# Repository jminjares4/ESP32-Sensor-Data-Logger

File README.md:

# ESP32-Sensor-Data-Logger

<div align='center'>

</div>

## **Hardware**

## **Mechanical**

* The housing was developed by [Rogelio Marco](https://github.com/RogelioMarco) :gear:.

## **Development**
|Microcontroller|Software|Enviroment|Operating System|
| :---| :---| :---| :---|
|  | |  | |

## **Author**
* [**Jesus Minjares** :zap:](https://github.com/jminjares4)<br>
  * Master of Science in Computer Engineering<br>

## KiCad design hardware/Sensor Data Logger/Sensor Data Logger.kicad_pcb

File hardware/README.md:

# Hardware

The hardware was developed through [KiCad](https://www.kicad.org) 6.0. 

## **Development**

## **Features**
- [x] USB-C Battery Charger
  - [x] 1.72 A max current charge
  - [x] Load protection
  - [x] Reverse current protection
- [x] Battery voltage reading 
- [x] MicroSD Card
  - [x] ESD Protection
- [x] Real-Time Clock 
  - [x] External power supply (CR2032)
- [x] External UART to flash ESP32 
- [x] I2C and Analog pins
- [x] Onboard status LEDs 
- [x] Testpoint
  - [x] 3.3V
  - [x] Vbat
  - [x] Ground

## **Schematic**

## **Printed Circuit Board**
### Front View

### Back View

## **Author**
* [**Jesus Minjares** :zap:](https://github.com/jminjares4)<br>
  * Master of Science in Computer Engineering<br>

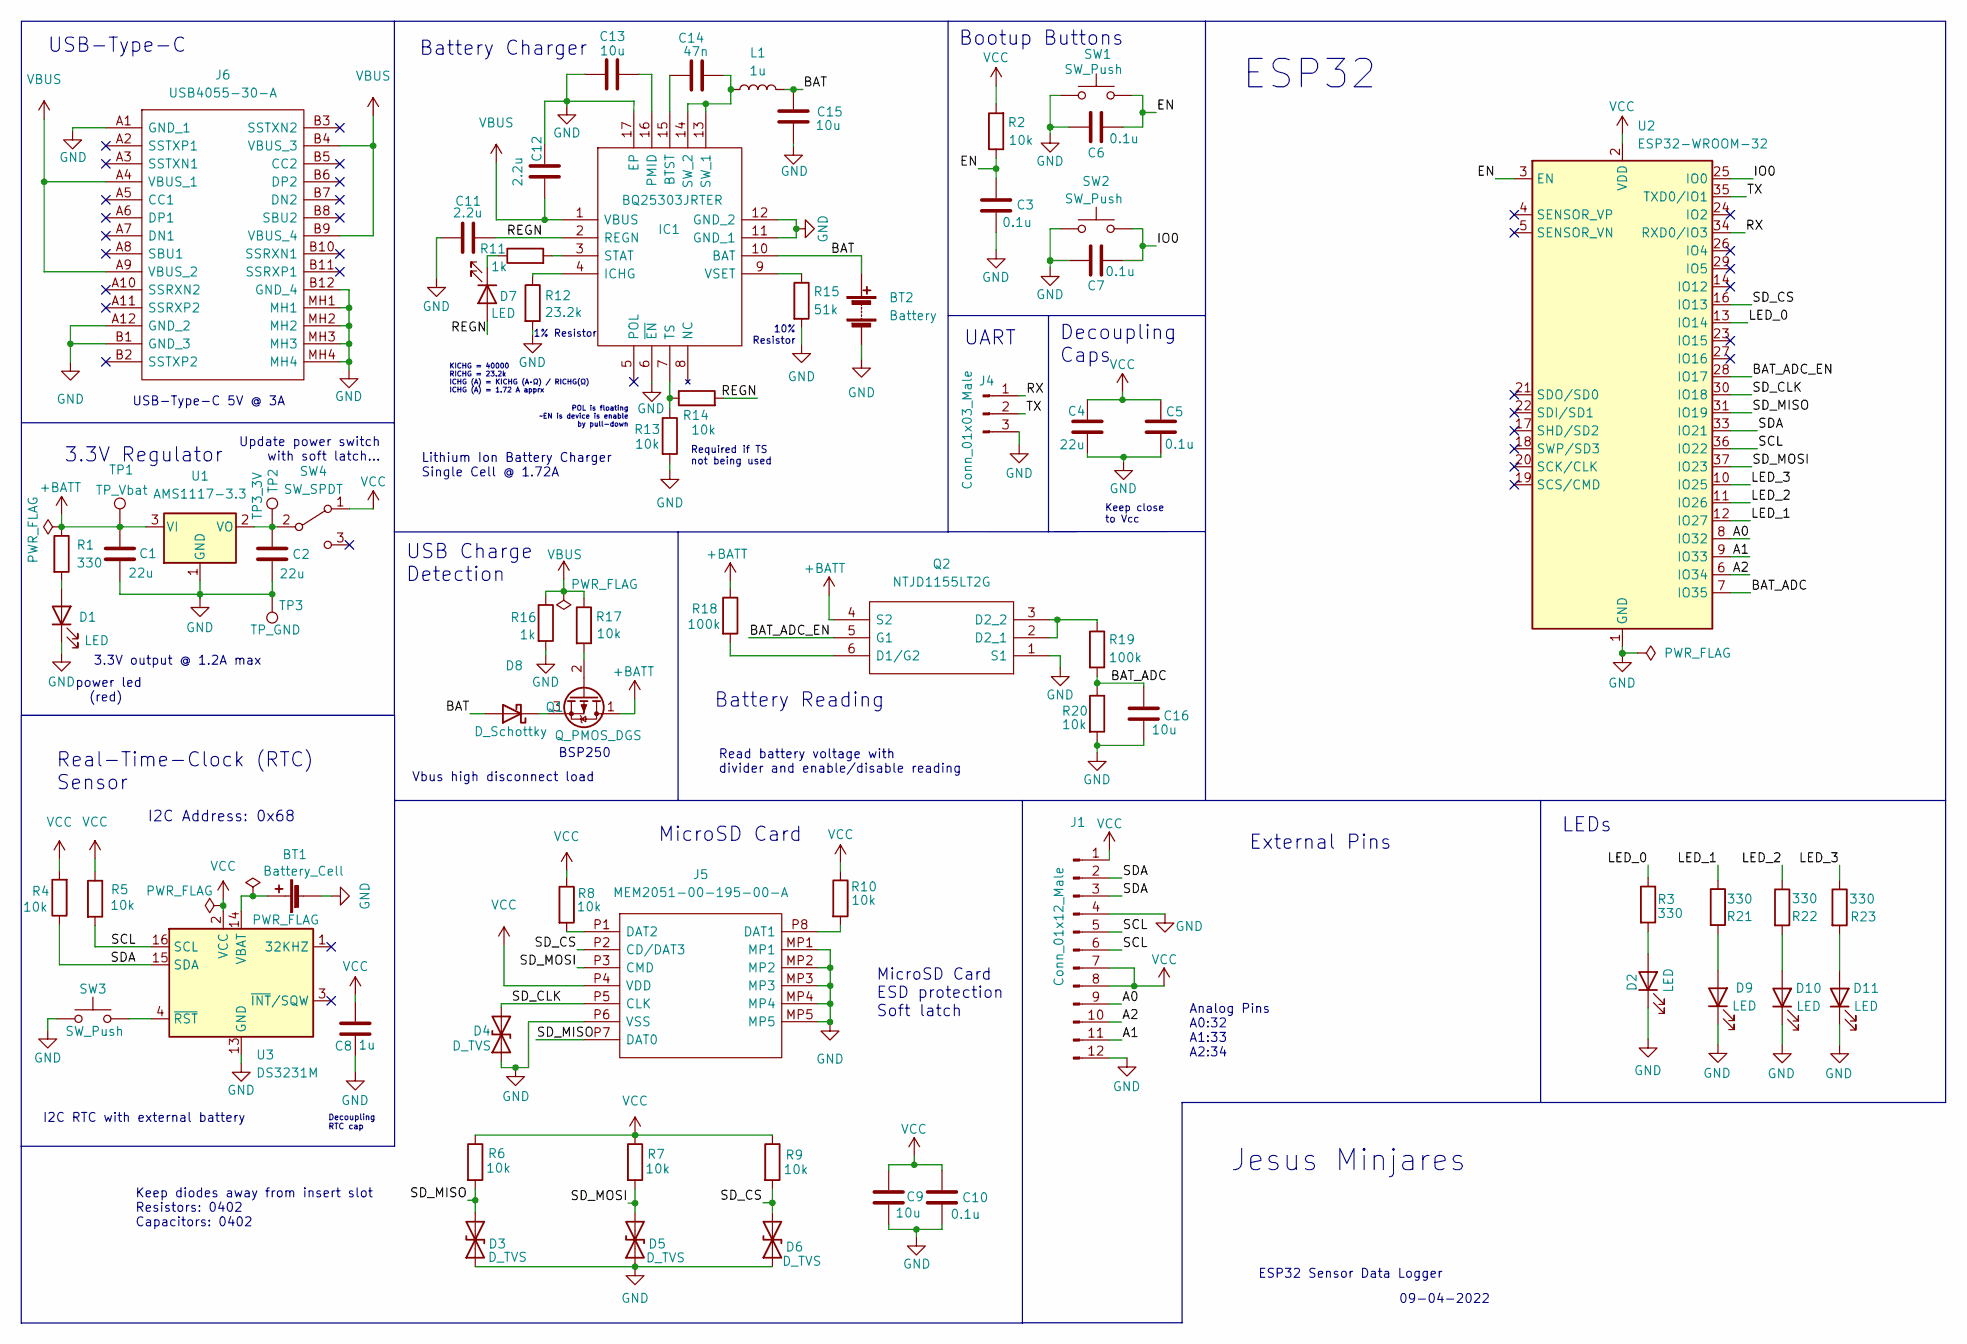
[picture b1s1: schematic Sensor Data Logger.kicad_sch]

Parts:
BT1: Battery_Cell; 3034
BT2: Battery; BatteryHolder_MPD_BH-18650-PC2
C1: 22u; C_0603_1608Metric
C2, C4: 22u; C_0402_1005Metric
C3, C5, C10: 0.1u; C_0402_1005Metric
C6, C7: 0.1u; C_0201_0603Metric
C8: 1u; C_0402_1005Metric
C9, C13: 10u; C_0402_1005Metric
C11: 2.2u; C_0603_1608Metric
C12: 2.2u; C_0402_1005Metric
C14: 47n; C_0402_1005Metric
C15: 10u; C_1206_3216Metric
C16: 10u; C_0603_1608Metric
D1, D2, D7, D9, D10, D11: LED; LED_0805_2012Metric
D3, D4, D5, D6: D_TVS; TPD1E10B06DPYR
D8: D_Schottky; D_0603_1608Metric
IC1: BQ25303JRTER; QFN50P300X300X80-17N-D; Manufacturer_Part_Number BQ25303JRTER; Mouser Part Number 595-BQ25303JRTER
J1: Conn_01x12_Male; PinHeader_2x06_P2.54mm_Vertical_SMD
J4: Conn_01x03_Male; PinHeader_1x03_P2.54mm_Vertical_SMD_Pin1Left
J5: MEM2051-00-195-00-A; MEM20510019500A; Manufacturer_Part_Number MEM2051-00-195-00-A; Mouser Part Number 640-MEM20510019500A
J6: USB4055-30-A; USB405530A; Manufacturer_Part_Number USB4055-30-A; Mouser Part Number 640-USB4055-30-A
L1: 1u; INDC3030X200N
Q1: Q_PMOS_DGS; SOT-223-3_TabPin2
Q2: NTJD1155LT2G; SOT65P210X110-6N; Manufacturer_Part_Number NTJD1155LT2G; Mouser Part Number 863-NTJD1155LT2G
R1, R3, R21, R22, R23: 330; R_0402_1005Metric
R2, R4, R5, R8, R10, R13, R14: 10k; R_0402_1005Metric
R6, R7, R9: 10k; R_0201_0603Metric
R11: 1k; R_0402_1005Metric
R12: 23.2k; R_0402_1005Metric
R15: 51k; R_0402_1005Metric
R16: 1k; R_0603_1608Metric
R17: 10k; R_0603_1608Metric
R18: 100k; R_0603_1608Metric
R19: 100k; R_0805_2012Metric
R20: 10k; R_0805_2012Metric
SW1, SW2, SW3: SW_Push; SW_SPST_B3U-1000P
SW4: SW_SPDT; SW_SPDT_PCM12
TP1: TP_Vbat; TestPoint_Pad_1.0x1.0mm
TP2: TP3_3V; TestPoint_Pad_1.0x1.0mm
TP3: TP_GND; TestPoint_Pad_1.0x1.0mm
U1: AMS1117-3.3; SOT-223-3_TabPin2
U2: ESP32-WROOM-32
U3: DS3231M; SOIC-16W_7.5x10.3mm_P1.27mm

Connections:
+BATT: C1.1, Q1.1 (D), Q2.4 (S2), R1.1, R18.1, TP1.1, U1.3 (VI)
/A0: J1.9, U2.8 (IO32)
/A1: J1.11, U2.9 (IO33)
/A2: J1.10, U2.6 (IO34)
/BAT: BT2.1 (+), C15.1, D8.2 (A), IC1.10 (BAT), L1.2
/BAT_ADC: C16.1, R19.2, R20.1, U2.7 (IO35)
/BAT_ADC_EN: Q2.5 (G1), U2.28 (IO17)
/EN: C3.1, C6.2, R2.1, SW1.2, U2.3 (EN)
/IO0: C7.2, SW2.2, U2.25 (IO0)
/LED_0: R3.1, U2.13 (IO14)
/LED_1: R21.1, U2.12 (IO27)
/LED_2: R22.1, U2.11 (IO26)
/LED_3: R23.1, U2.10 (IO25)
/REGN: C11.2, D7.2 (A), IC1.2 (REGN), R14.2
/RX: J4.1, U2.34 (RXD0/IO3)
/SCL: J1.5, J1.6, R5.2, U2.36 (IO22), U3.16 (SCL)
/SDA: J1.2, J1.3, R4.1, U2.33 (IO21), U3.15 (SDA)
/SD_CLK: D4.2 (A2), J5.P5 (CLK), U2.30 (IO18)
/SD_CS: D6.2 (A2), J5.P2 (CD/DAT3), R9.2, U2.16 (IO13)
/SD_MISO: D3.2 (A2), J5.P7 (DAT0), R6.2, U2.31 (IO19)
/SD_MOSI: D5.2 (A2), J5.P3 (CMD), R7.2, U2.37 (IO23)
/TX: J4.2, U2.35 (TXD0/IO1)
unnamed: C2.1, SW4.2 (B), TP2.1, U1.2 (VO)
unnamed: C6.1, SW1.1
unnamed: C7.1, SW2.1
unnamed: C13.1, IC1.16 (PMID)
unnamed: C14.1, IC1.15 (BTST)
unnamed: C14.2, IC1.13 (SW_1), IC1.14 (SW_2), L1.1
unnamed: D1.2 (A), R1.2
unnamed: D2.2 (A), R3.2
unnamed: D7.1 (K), R11.1
unnamed: D8.1 (K), Q1.3 (S)
unnamed: D9.2 (A), R21.2
unnamed: D10.2 (A), R22.2
unnamed: D11.2 (A), R23.2
unnamed: IC1.3 (STAT), R11.2
unnamed: IC1.4 (ICHG), R12.1
unnamed: IC1.7 (TS), R13.1, R14.1
unnamed: IC1.9 (VSET), R15.1
unnamed: J5.MP1, J5.MP2, J5.MP3, J5.MP4, J5.MP5
unnamed: J5.P1 (DAT2), R8.2
unnamed: J5.P8 (DAT1), R10.2
unnamed: Q1.2 (G), R17.2
unnamed: Q2.2 (D2_1), Q2.3 (D2_2), R19.1
unnamed: Q2.6 (D1/G2), R18.2
unnamed: SW3.2, U3.4 (~RST)
VBUS: C12.2, IC1.1 (VBUS), J6.A4 (VBUS_1), J6.A9 (VBUS_2), J6.B4 (VBUS_3), J6.B9 (VBUS_4), R16.1, R17.1
VCC: C4.1, C5.1, C8.1, C9.1, C10.1, J1.1, J1.7, J1.8, J5.P4 (VDD), R2.2, R4.2, R5.1, R6.1, R7.1, R8.1, R9.1, R10.1, SW4.1 (A), U2.2 (VDD), U3.2 (VCC)

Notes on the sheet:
Keep diodes away from insert slot Resistors: 0402 Capacitors: 0402
MicroSD Card
ESP32 Sensor Data Logger
Required if TS not being used
Vbus high disconnect load
Update power switch with soft latch...
UART
POL is floating ~EN is device is enable by pull-down
3.3V output @ 1.2A max
ESP32
BSP250
Jesus Minjares
10% Resistor
USB-Type-C 5V @ 3A
External Pins
USB-Type-C
Read battery voltage with divider and enable/disable reading
1% Resistor
Decoupling Caps
3.3V Regulator
LEDs
Keep close to Vcc
I2C RTC with external battery
KICHG = 40000 RICHG = 23.2k ICHG (A) = KICHG (A·Ω) / RICHG(Ω) ICHG (A) = 1.72 A apprx
Bootup Buttons
09-04-2022
Lithium Ion Battery Charger Single Cell @ 1.72A
Battery Reading
Real-Time-Clock (RTC) Sensor
I2C Address: 0x68
Decoupling RTC cap
Analog Pins A0:32 A1:33 A2:34
Battery Charger
MicroSD Card ESD protection Soft latch
power led (red)
USB Charge Detection

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
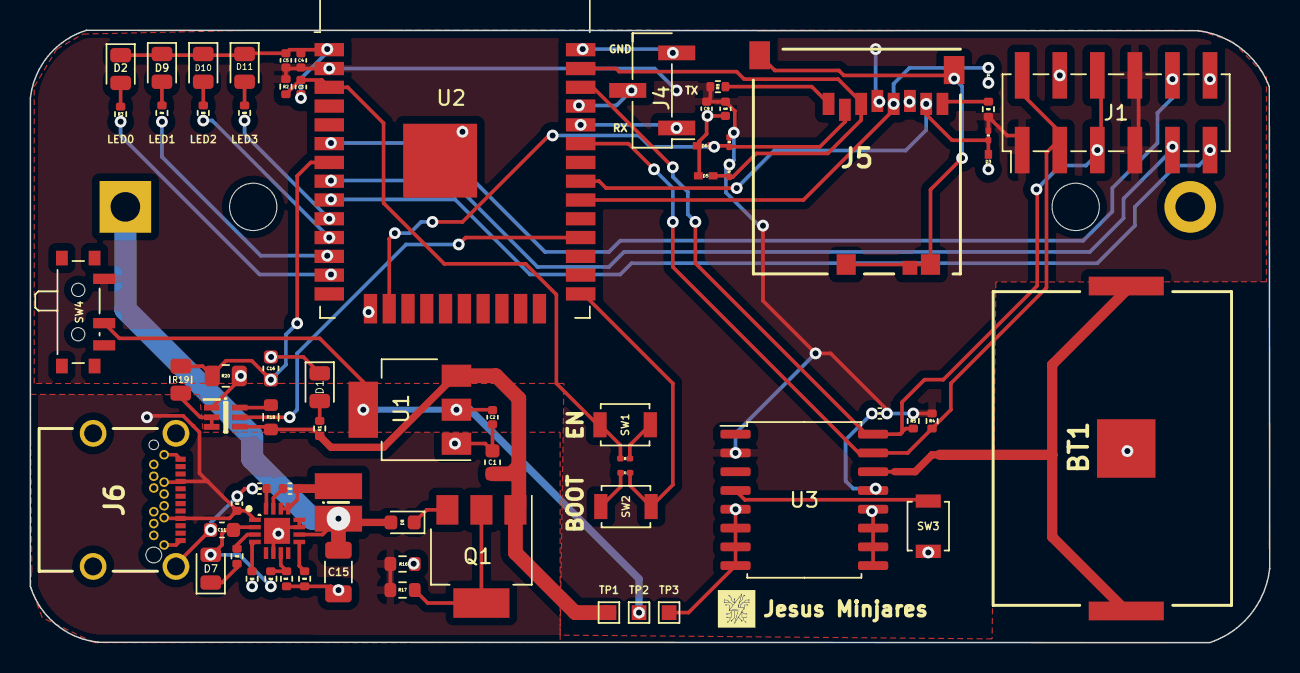
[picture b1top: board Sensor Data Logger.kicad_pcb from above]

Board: 2 copper layers, 83.8 x 41.4 mm, 70 parts (1 on the bottom side), 50 nets.

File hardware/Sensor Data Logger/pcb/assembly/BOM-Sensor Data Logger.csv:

Comment,Designator,Footprint,LCSC
100k,R18,R_0603_1608Metric,
D_TVS,D3,TPD1E10B06DPYR,
10u,C16,C_0603_1608Metric,
330,R1,R_0402_1005Metric,
AMS1117-3.3,U1,SOT-223-3_TabPin2,
10k,R6,R_0201_0603Metric,
D_TVS,D5,TPD1E10B06DPYR,
0.1u,C6,C_0201_0603Metric,
SW_SPDT,SW4,SW_SPDT_PCM12,
LED,D10,LED_0805_2012Metric,
330,R21,R_0402_1005Metric,
1k,R11,R_0402_1005Metric,
TP_Vbat,TP1,TestPoint_Pad_1.0x1.0mm,
Conn_01x12_Male,J1,PinHeader_2x06_P2.54mm_Vertical_SMD,
SW_Push,SW2,SW_SPST_B3U-1000P,
D_TVS,D4,TPD1E10B06DPYR,
23.2k,R12,R_0402_1005Metric,
10u,C9,C_0402_1005Metric,
10k,R4,R_0402_1005Metric,
10k,R13,R_0402_1005Metric,
USB4055-30-A,J6,USB405530A,
1u,C8,C_0402_1005Metric,
TP3_3V,TP2,TestPoint_Pad_1.0x1.0mm,
0.1u,C5,C_0402_1005Metric,
10k,R7,R_0201_0603Metric,
330,R23,R_0402_1005Metric,
MEM2051-00-195-00-A,J5,MEM20510019500A,
10k,R8,R_0402_1005Metric,
51k,R15,R_0402_1005Metric,
Battery_Cell,BT1,3034,
2.2u,C11,C_0603_1608Metric,
SW_Push,SW3,SW_SPST_B3U-1000P,
ESP32-WROOM-32,U2,ESP32-WROOM-32,
22u,C2,C_0402_1005Metric,
330,R3,R_0402_1005Metric,
NTJD1155LT2G,Q2,SOT65P210X110-6N,
22u,C4,C_0402_1005Metric,
0.1u,C7,C_0201_0603Metric,
D_TVS,D6,TPD1E10B06DPYR,
10k,R20,R_0805_2012Metric,
LED,D9,LED_0805_2012Metric,
Q_PMOS_DGS,Q1,SOT-223-3_TabPin2,
LED,D7,LED_0805_2012Metric,
1k,R16,R_0603_1608Metric,
BQ25303JRTER,IC1,QFN50P300X300X80-17N-D,
LED,D2,LED_0805_2012Metric,
100k,R19,R_0805_2012Metric,
LED,D11,LED_0805_2012Metric,
0.1u,C10,C_0402_1005Metric,
330,R22,R_0402_1005Metric,
10u,C15,C_1206_3216Metric,
SW_Push,SW1,SW_SPST_B3U-1000P,
10k,R10,R_0402_1005Metric,
10k,R14,R_0402_1005Metric,
10k,R5,R_0402_1005Metric,
Conn_01x03_Male,J4,PinHeader_1x03_P2.54mm_Vertical_SMD_Pin1Left,
D_Schottky,D8,D_0603_1608Metric,
10u,C13,C_0402_1005Metric,
1u,L1,INDC3030X200N,
LED,D1,LED_0805_2012Metric,
TP_GND,TP3,TestPoint_Pad_1.0x1.0mm,
10k,R17,R_0603_1608Metric,
DS3231M,U3,SOIC-16W_7.5x10.3mm_P1.27mm,
0.1u,C3,C_0402_1005Metric,
22u,C1,C_0603_1608Metric,
2.2u,C12,C_0402_1005Metric,
47n,C14,C_0402_1005Metric,
10k,R9,R_0201_0603Metric,
10k,R2,R_0402_1005Metric,
Battery,BT2,BatteryHolder_MPD_BH-18650-PC2,

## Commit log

2022-07-08 Added gitignore for esp-idf and c
2022-07-08 Added blinky example as template code
2022-07-08 Update to latest commit
2022-07-23 Update led example with correct gpio function calls
2022-07-24 Added serial monitor to avoid using putty/screen
2022-07-24 Documented monitor.py
2022-07-24 Remove extra package
2022-08-05 Update cmake to build drivers
2022-08-05 Added include folder
2022-08-05 Added src folder
2022-08-05 Changed main.c
2022-08-05 Move tools path
2022-08-10 Added button.h
2022-08-10 Added button.c
2022-08-10 Update main and cmake to build and use latest drivers
2022-08-10 remove previous comments
2022-08-16 Added build esp-idf
2022-08-16 Remove sdkconfig
2022-08-16 Added badges
2022-08-16 Changed drivers paths
2022-08-16 Edit default readme
2022-08-16 Updated main.c
2022-08-16 Added devices source in cmake
2022-08-16 Update devices path and change cmake
2022-08-17 Added esp-idf v4.2-v4.4
2022-08-17 Added esp-idf version check
2022-08-17 Fix esp-idf v4.x error
2022-08-17 Fix bug
2022-08-17 Redid led_toggle
2022-08-17 Changed esp_rom_printf to printf
2022-08-20 Added lcd driver
2022-08-20 Added lcd driver to cmake
2022-08-20 Create lcd task
2022-08-20 Added lcd driver files to devices
2022-08-20 Fix build action workflow
2022-08-20 Changed custom text
2022-08-20 Remove gps driver
2022-08-20 Removed gps files from cmake
2022-08-23 Added extra components
2022-08-23 Updated with new components
2022-08-23 Changed drivers paths to components
2022-08-24 Added esp-idf-lib submodule
2022-08-24 Added new components
2022-08-24 Create new task with esp-idf-lib drivers
2022-08-24 Fix format
2022-08-24 Changed %lu to PRIu32
2022-08-25 Added esp32 pin selection
2022-08-25 Added doxygen action workflow
2022-08-25 Added custom layout
2022-08-25 Added mainpage.md
2022-08-25 Added doxygen documentation to components
2022-08-25 Added jminjares4 logo
2022-08-25 Added Doxyfile
2022-08-25 Ignore doxygen build
2022-08-25 deploy: 593d569593612f890aa96b96b33bcb24c0ab7e88
2022-08-25 Added action workflow badges
2022-08-25 deploy: a4e3b10fe48c86fa7f8fb0c9d21b4c7ead431200
2022-08-26 Added new ssd1306 driver as submodule
2022-08-26 Updated cmake to use new driver
2022-08-26 Created a new task to display bmp180 to oled
2022-08-26 Added submodule drivers to project
2022-08-26 Data conversion: c->f
2022-08-26 deploy: fb818827f03ee39e7dfcaa5c05bdd4b90075db81
2022-08-27 Changed submodule paths to clean folder
2022-08-27 deploy: c95321daef11b10bc59a9520b51e0b406dbf82a0
2022-08-27 Remove old path
2022-08-27 Added rtc driver
2022-08-27 deploy: 05bfce0638a5775e80fcf7636cc4760b61566ec9
2022-08-27 Formatted main.c
2022-08-28 Added sdcard task
2022-08-28 deploy: b8420956b07e1c1dc9ddd58c87c4c9bbd291128c
2022-08-28 Fix esp-idf spi version
2022-08-28 deploy: aa9818c43215e111ef0974d2f5229dbf5479fc62
2022-08-28 Removed esp-idf v4.2 build
2022-08-29 Added esp timer task
2022-08-29 deploy: b196d30e7fe955a87333ae5d17875bac32e4478f
2022-08-29 Added notification handles to synchronize tasks
2022-08-29 Fix %d -> %lu
2022-08-31 Updated doxygen paths
2022-08-31 Changed custom pages and layout to single folder
2022-08-31 Moved to documentation/
2022-08-31 deploy: 9ad918de4a1726e37555d4ef126d6556e90a230c
2022-08-31 Added generic queue
2022-08-31 deploy: 8b4dcbdabb0b4c848c97837fd6154d6b51b92295
2022-08-31 Added comments
2022-09-01 Added battery task
2022-09-01 Added new component to CMakeLists.txt
2022-09-01 Added new battery driver
2022-09-01 deploy: 4fd1c8f8b8afaeb3c024302dd1666a0ad30c5458
2022-09-01 Edit action workflow for only ESP32
2022-09-03 Changed adc default channel
2022-09-03 deploy: 04548a6c26674d10b8013c964eeeea3448d63da8
2022-09-03 Added current schematic: esp32, 3.3v ldo, i2c, analog pins, and rtc
2022-09-06 Added schematic
2022-09-06 Latest schematic
2022-09-06 Update battery adc enable pin
2022-09-07 Latest hardware changes
2022-09-07 deploy: 319846aa0c11cc27058df5bb3110f1dc13df6131
2022-09-07 Added initial hardware markdown
2022-09-07 deploy: cc2cd1c67238fc90f5378a76edae231c773219e9
2022-09-07 Added schematic.pdf
2022-09-07 deploy: a96d1c5b87bded0783d28997d663ce835878f1b0
2022-09-07 Changed pdf implementation
2022-09-07 deploy: 85c771678196be5a80e44f343391e96632b26143
2022-09-07 deploy: 37a41dcfa4faf4dd52b9540464f7367f00bbaf68
2022-09-07 deploy: 6dc88699f43265da94dcede3ca96c729892ced68
2022-09-07 Removed oled
2022-09-07 deploy: 7d558177d98bbbdccc5c5b69036edb766b3bbbb8
2022-09-11 Ignore backup files
2022-09-11 Update latest hardware changes
2022-09-11 deploy: 9cc9288263ee4cc6da0abae737593a84b4e076bb
2022-09-11 Remove old backup files
2022-09-11 Changed path
2022-09-11 Update layout
2022-09-11 deploy: 7e1a187c15ef6c428cb65b0c513b1ff2fb3813d1
2022-09-11 Update libraries
2022-09-11 deploy: fb8697649360608cdfb1e9e20280dcea25c80efd
2022-09-11 Remove zap
2022-09-11 deploy: 28e92fd6ba4a2fde6412f3da8d5fc1b9746207d1
2022-09-11 Updated documentation
2022-09-11 deploy: dd9dcabd2c0ca1bb5e5245d2459ac9e615a6c099
2022-09-11 Default doxygen-awesome-css layout
2022-09-11 deploy: bd7367069c53a2c06d6f7659ae84d36c89f9fccd
2022-09-11 Added 4k video
2022-09-11 deploy: 691b9c3f224e4b775db249faf280129a0f1907a2
2022-09-11 Change 4k to gif
2022-09-12 Trimmed video
2022-09-12 deploy: e58ee5be5451318ac17a94aa5101876e80c5d0a7
2022-09-13 Added step file
2022-09-13 Remove stl file
2022-09-21 Added mechanical housing
2022-09-21 Update readme and added rogelio as contributor
2022-09-21 Fix submodule image path
2022-09-21 Update image to relative path
